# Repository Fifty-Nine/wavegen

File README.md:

Introduction
============

This is an implementation of a USB-controlled Analog Devices AD9837-based 
function generator that can generate sine, triangle and square waves up to 
around 200 kHz or so, 1 MHz if the output filtering capacitor is removed
(although the quantization of the ADC starts to become apparent around
500 kHz).

Connectors, Jumpers and Indicators
==================================

There are several off-board connectors, one jumper and three
LEDs.

| Reference    | Purpose                                    |
| ------------ | ------------------------------------------ |
| J1           | Micro-B USB Connector                      |
| J2           | External clock input                       |
| J3           | Function generator output (0.6Vpp typical) |
| J4           | FTDI channel B breakout                    |
| TP1          | USB supply voltage (5V typical, 15V max)   |
| TP2          | GND                                        |
| TP3          | LD1117 output (3.3V nominal)               |
| TP4          | Function generator output (0.6Vpp typical  |
| JP1          | Clock select jumper                        |
| D1           | LD1117 power indicator                     |
| D2           | Currently unused                           |
| D3           | Currently unused                           |

At some point I'll document the pinout for the J4 connector here.
Until then the pinout is available in the schematic.

Indicators D2 and D3 were originally intended as SPI TX/RX indicators, but
that was before I realized that the FT2232H only enables them for UART
communication (and also that the AD 9837 has no TX...). There's nothing
stopping the control software from using them for other purposes, although
the silkscreen on rev. 2 would be misleading.

Firmware
========

Because the design is based on the FTDI FT2232H, there's no firmware per se.
However, the control software looks for certain USB product and manufacturer
strings to differentiate the device from other FTDI devices. A template for
the FTDI 'FT_Prog' EEPROM programming software is provided in the `firmware/`
directory. The device should be programmed with this template before attempting
to use the control software.

Control Software
================

The control software is a work in progress, but the device can currently be
fully controlled via a provided software library. The library is written in
C++ and requires a compiler with C++11 support.

To build the library, you will need CMake and a suitable C++ compiler. On
linux, the build steps go something like this:

```
$ sudo apt-get install git build-essential cmake libftdi-dev
...
$ git clone git@github.com:Fifty-Nine/wavegen
...
$ cd wavegen/software
$ mkdir build
$ cd build
$ cmake ..
...
$ make
...
$ sudo make install
...
$
```

At this point, you can use the `wavegen-test` program to confirm that the device
is working. The test program initializes the device and repeatedly performs a
frequency sweep.

Future Work
===========

A GUI control interface would be nice to have. 

One major limitation of the current hardware is that it provides no output
amplitude control or amplification. At some point I would like to design
an amplification stage with automatic gain control. Rev 3 will allow
arbitrary waveform generation, so this will be mitigated somewhat.

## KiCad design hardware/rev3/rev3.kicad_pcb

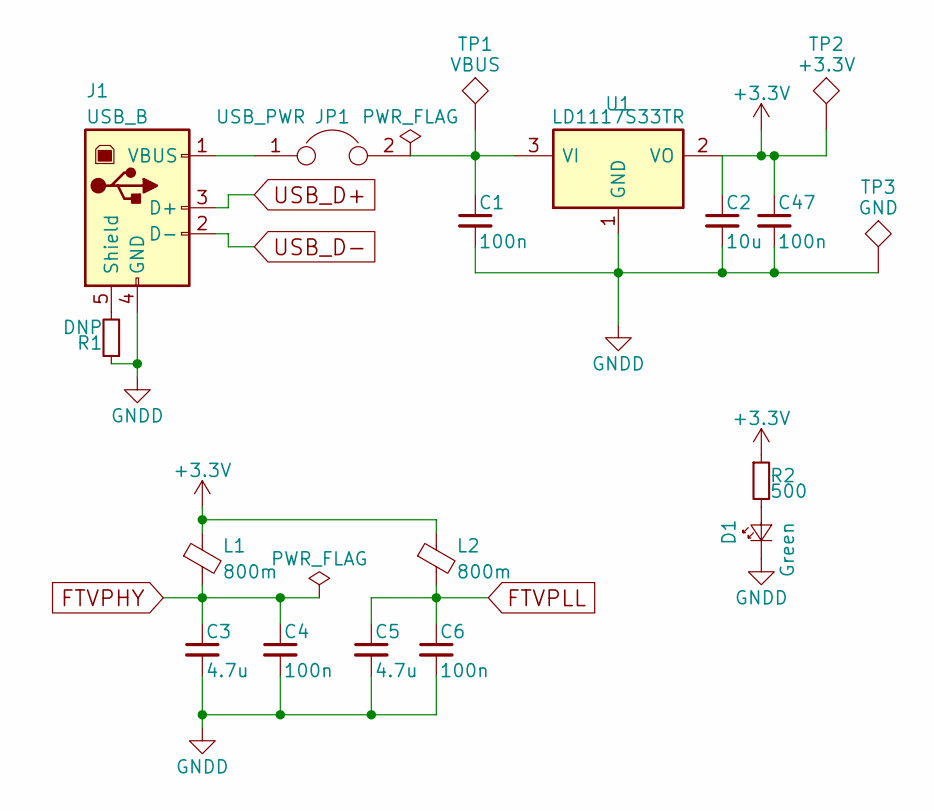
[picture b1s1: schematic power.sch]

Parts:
C1, C4, C6, C47: 100n; C_0603_HandSoldering; DigiKey 478-1395-1-ND
C2: 10u; C_0603_HandSoldering; DigiKey 478-10568-1-ND
C3, C5: 4.7u; C_0603_HandSoldering; DigiKey 478-1415-1-ND
D1: Green; LED_0805; DigiKey 350-2900-ND
J1: USB_B; USB_Micro-B-circular; DigiKey 609-4618-1-ND
JP1: USB_PWR; Pin_Header_Straight_1x02_Pitch2.54mm
L1, L2: 800m; L_0603_HandSoldering; DigiKey 490-1054-1-ND
R1: DNP; R_0603_HandSoldering; DigiKey DNP
R2: 500; R_0603_HandSoldering; DigiKey P470ADCT-ND
TP1: VBUS; Test_Point_Keystone_5005-5009_Compact; DigiKey 36-5009-ND
TP2: +3.3V; Test_Point_Keystone_5005-5009_Compact; DigiKey 36-5005-ND
TP3: GND; Test_Point_Keystone_5005-5009_Compact; DigiKey 36-5006-ND
U1: LD1117S33TR; SOT-223; DigiKey 497-1242-1-ND

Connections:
+3V3: C2.1, C47.1, L1.1, L2.1, R2.1, TP2.1, U1.2 (VO); also elsewhere on the board
FTVPHY: C3.1, C4.1, L1.2; also elsewhere on the board
FTVPLL: C5.1, C6.1, L2.2; also elsewhere on the board
GNDA: C1.2, C2.2, C3.2, C4.2, C5.2, C6.2, C47.2, D1.1 (K), J1.4 (GND), R1.1, TP3.1, U1.1 (GND); also elsewhere on the board
unnamed: C1.1, JP1.2, TP1.1, U1.3 (VI)
unnamed: D1.2 (A), R2.2
unnamed: J1.1 (VBUS), JP1.1
unnamed: J1.5 (Shield), R1.2
USB_D+: J1.3 (D+); also elsewhere on the board
USB_D-: J1.2 (D-); also elsewhere on the board

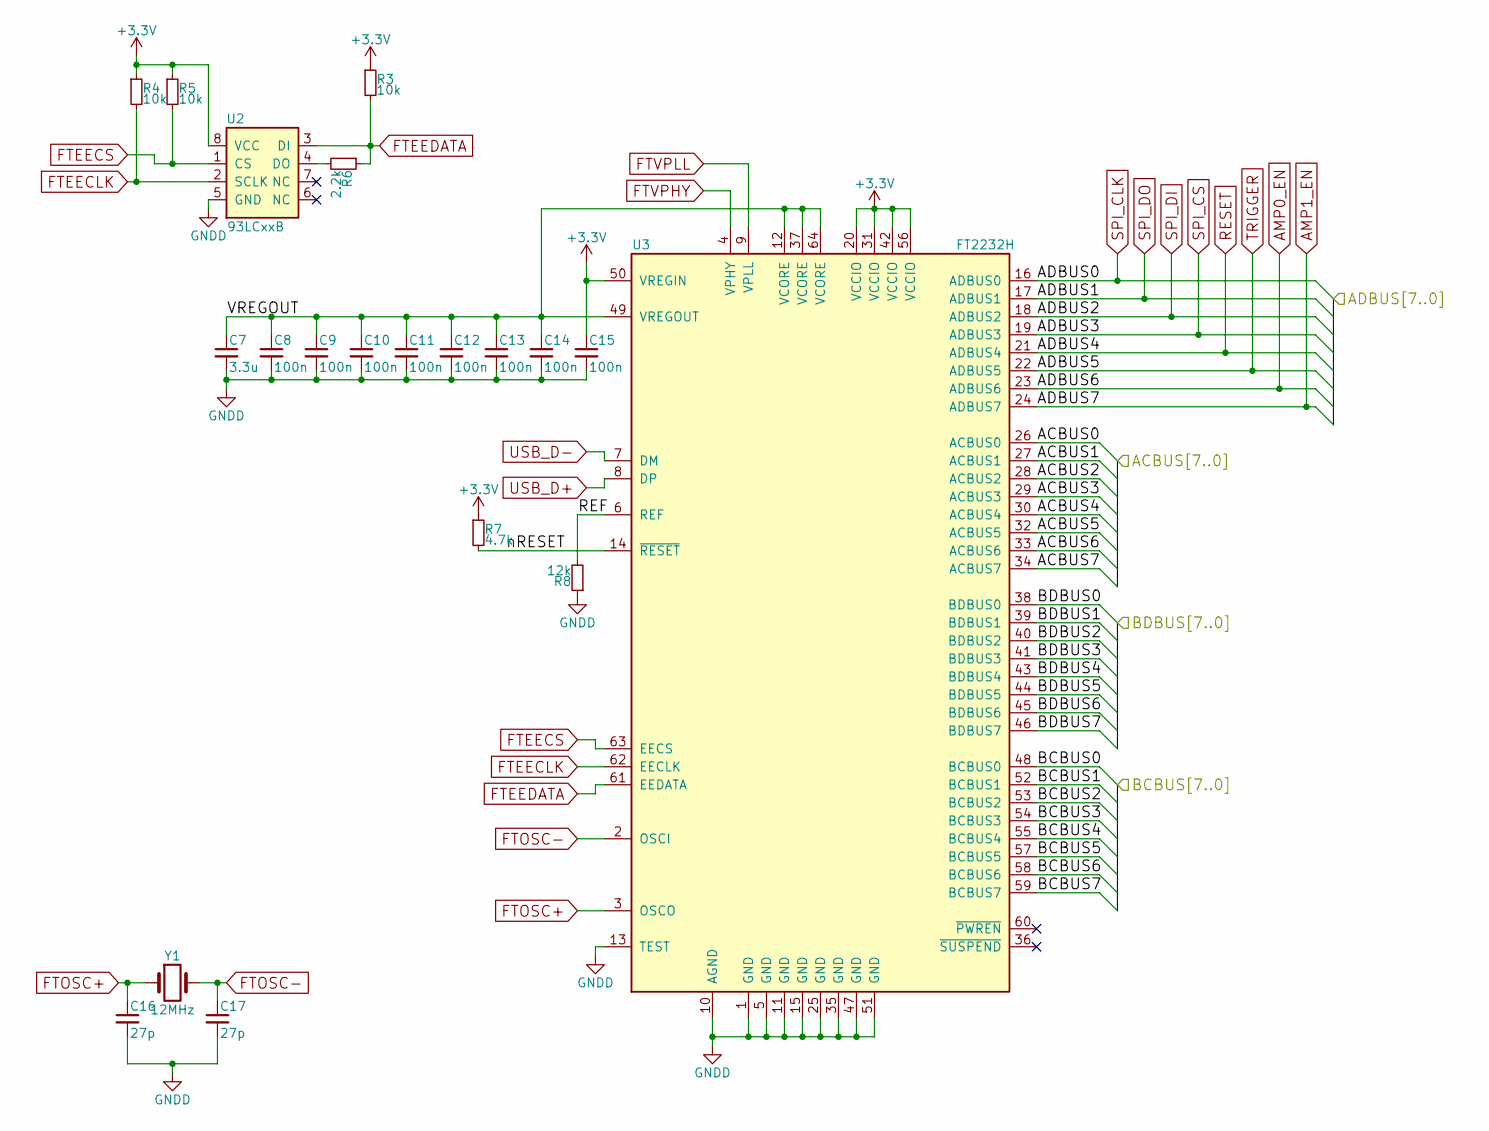
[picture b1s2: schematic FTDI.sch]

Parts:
C7: 3.3u; C_0805; DigiKey 478-1414-1-ND
C8, C9, C10, C11, C12, C13, C14, C15: 100n; C_0805; DigiKey 478-1395-1-ND
C16, C17: 27p; C_0805; DigiKey 478-10518-1-ND
R3, R4, R5: 10k; R_0805; DigiKey P10KADCT-ND
R6: 2.2k; R_0805; DigiKey P2.2KADCT-ND
R7: 4.7k; R_0805; DigiKey P1.0KADCT-ND
R8: 12k; R_0805; DigiKey P12KADCT-ND
U2: 93LCxxB; SOIC-8_3.9x4.9mm_Pitch1.27mm; DigiKey 93LC46B/SN-ND
U3: FT2232H; LQFP-64_10x10mm_Pitch0.5mm
Y1: 12MHz; Crystal_SMD_5032-2pin_5.0x3.2mm; DigiKey 535-10634-1-ND

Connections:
+3V3: C15.1, R3.1, R4.1, R5.1, R7.1, U2.8 (VCC), U3.20 (VCCIO), U3.31 (VCCIO), U3.42 (VCCIO), U3.50 (VREGIN), U3.56 (VCCIO); also elsewhere on the board
/Connectors/ACBUS0: U3.26 (ACBUS0); also elsewhere on the board
/Connectors/ACBUS1: U3.27 (ACBUS1); also elsewhere on the board
/Connectors/ACBUS2: U3.28 (ACBUS2); also elsewhere on the board
/Connectors/ACBUS3: U3.29 (ACBUS3); also elsewhere on the board
/Connectors/ACBUS4: U3.30 (ACBUS4); also elsewhere on the board
/Connectors/ACBUS5: U3.32 (ACBUS5); also elsewhere on the board
/Connectors/ACBUS6: U3.33 (ACBUS6); also elsewhere on the board
/Connectors/ACBUS7: U3.34 (ACBUS7); also elsewhere on the board
/Connectors/BCBUS0: U3.48 (BCBUS0); also elsewhere on the board
/Connectors/BCBUS1: U3.52 (BCBUS1); also elsewhere on the board
/Connectors/BCBUS2: U3.53 (BCBUS2); also elsewhere on the board
/Connectors/BCBUS3: U3.54 (BCBUS3); also elsewhere on the board
/Connectors/BCBUS4: U3.55 (BCBUS4); also elsewhere on the board
/Connectors/BCBUS5: U3.57 (BCBUS5); also elsewhere on the board
/Connectors/BCBUS6: U3.58 (BCBUS6); also elsewhere on the board
/Connectors/BCBUS7: U3.59 (BCBUS7); also elsewhere on the board
/Connectors/BDBUS0: U3.38 (BDBUS0); also elsewhere on the board
/Connectors/BDBUS1: U3.39 (BDBUS1); also elsewhere on the board
/Connectors/BDBUS2: U3.40 (BDBUS2); also elsewhere on the board
/Connectors/BDBUS3: U3.41 (BDBUS3); also elsewhere on the board
/Connectors/BDBUS4: U3.43 (BDBUS4); also elsewhere on the board
/Connectors/BDBUS5: U3.44 (BDBUS5); also elsewhere on the board
/Connectors/BDBUS6: U3.45 (BDBUS6); also elsewhere on the board
/Connectors/BDBUS7: U3.46 (BDBUS7); also elsewhere on the board
/FTDI/REF: R8.2, U3.6 (REF)
/FTDI/VREGOUT: C7.1, C8.1, C9.1, C10.1, C11.1, C12.1, C13.1, C14.1, U3.12 (VCORE), U3.37 (VCORE), U3.49 (VREGOUT), U3.64 (VCORE)
/FTDI/nRESET: R7.2, U3.14 (~RESET)
AMP0_EN: U3.23 (ADBUS6); also elsewhere on the board
AMP1_EN: U3.24 (ADBUS7); also elsewhere on the board
FTEECLK: R4.2, U2.2 (SCLK), U3.62 (EECLK)
FTEECS: R5.2, U2.1 (CS), U3.63 (EECS)
FTEEDATA: R3.2, R6.1, U2.3 (DI), U3.61 (EEDATA)
FTOSC+: C16.1, U3.3 (OSCO), Y1.1
FTOSC-: C17.1, U3.2 (OSCI), Y1.2
FTVPHY: U3.4 (VPHY); also elsewhere on the board
FTVPLL: U3.9 (VPLL); also elsewhere on the board
GNDA: C7.2, C8.2, C9.2, C10.2, C11.2, C12.2, C13.2, C14.2, C15.2, C16.2, C17.2, R8.1, U2.5 (GND), U3.1 (GND), U3.5 (GND), U3.10 (AGND), U3.11 (GND), U3.13 (TEST), U3.15 (GND), U3.25 (GND), U3.35 (GND), U3.47 (GND), U3.51 (GND); also elsewhere on the board
unnamed: R6.2, U2.4 (DO)
RESET: U3.21 (ADBUS4); also elsewhere on the board
SPI_CLK: U3.16 (ADBUS0); also elsewhere on the board
SPI_CS: U3.19 (ADBUS3); also elsewhere on the board
SPI_DI: U3.18 (ADBUS2); also elsewhere on the board
SPI_DO: U3.17 (ADBUS1); also elsewhere on the board
TRIGGER: U3.22 (ADBUS5); also elsewhere on the board
USB_D+: U3.8 (DP); also elsewhere on the board
USB_D-: U3.7 (DM); also elsewhere on the board

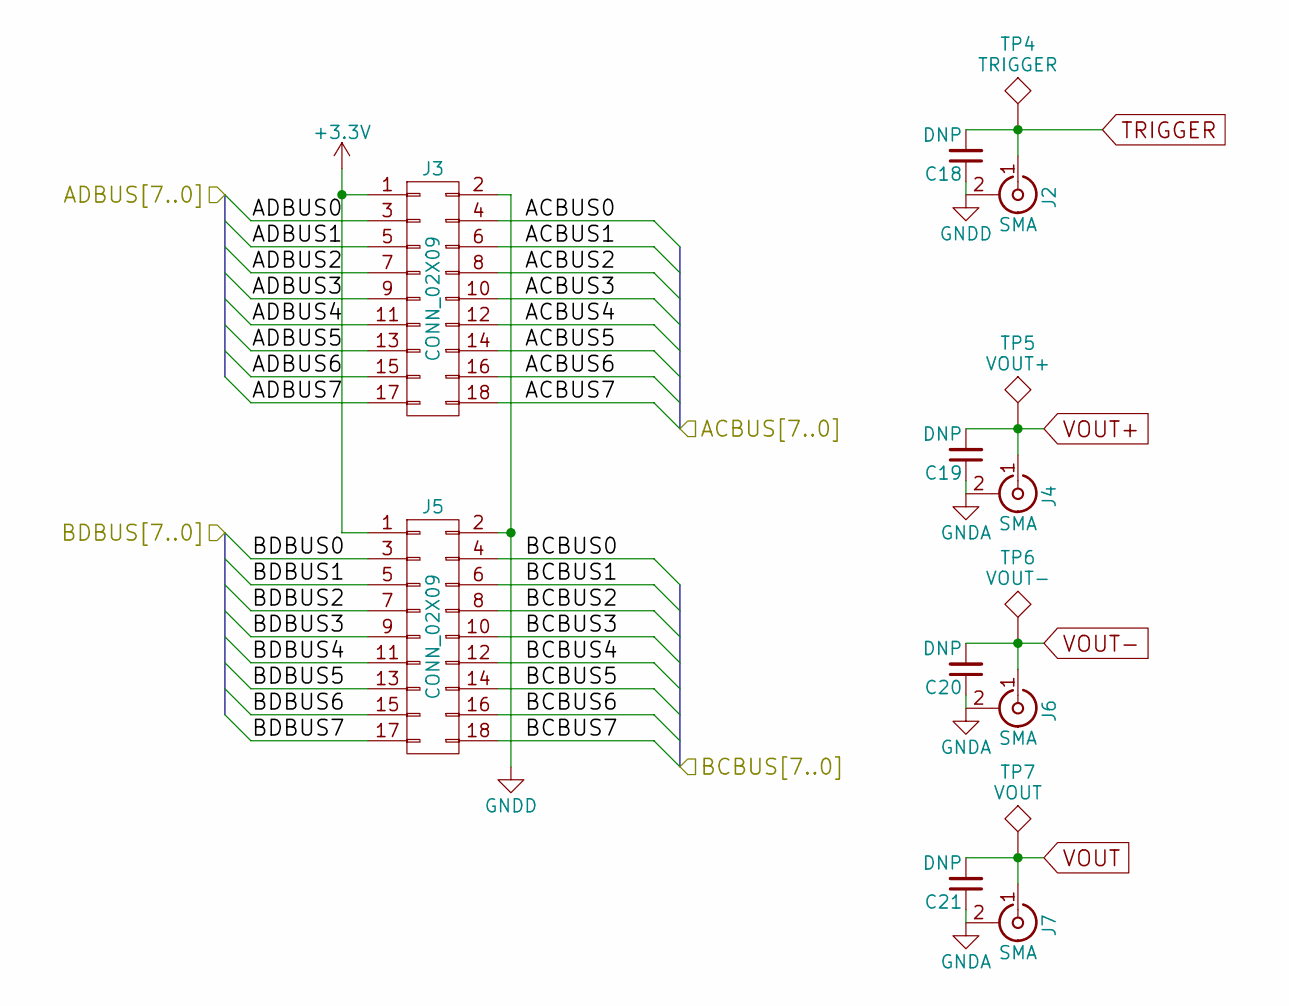
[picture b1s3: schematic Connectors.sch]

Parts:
C18, C19, C20, C21: DNP; C_0603_HandSoldering
J2: SMA; SMA_THT_Jack_Straight
J3, J5: CONN_02X09; Pin_Header_Straight_2x09_Pitch2.54mm; DigiKey S2011EC-40-ND
J4, J6, J7: SMA; Molex_SMA_Jack_Edge_Mount
TP4: TRIGGER; Test_Point_Keystone_5005-5009_Compact
TP5: VOUT+; Test_Point_Keystone_5005-5009_Compact
TP6: VOUT-; Test_Point_Keystone_5005-5009_Compact
TP7: VOUT; Test_Point_Keystone_5005-5009_Compact

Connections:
+3V3: J3.1, J5.1; also elsewhere on the board
/Connectors/ACBUS0: J3.4; also elsewhere on the board
/Connectors/ACBUS1: J3.6; also elsewhere on the board
/Connectors/ACBUS2: J3.8; also elsewhere on the board
/Connectors/ACBUS3: J3.10; also elsewhere on the board
/Connectors/ACBUS4: J3.12; also elsewhere on the board
/Connectors/ACBUS5: J3.14; also elsewhere on the board
/Connectors/ACBUS6: J3.16; also elsewhere on the board
/Connectors/ACBUS7: J3.18; also elsewhere on the board
/Connectors/BCBUS0: J5.4; also elsewhere on the board
/Connectors/BCBUS1: J5.6; also elsewhere on the board
/Connectors/BCBUS2: J5.8; also elsewhere on the board
/Connectors/BCBUS3: J5.10; also elsewhere on the board
/Connectors/BCBUS4: J5.12; also elsewhere on the board
/Connectors/BCBUS5: J5.14; also elsewhere on the board
/Connectors/BCBUS6: J5.16; also elsewhere on the board
/Connectors/BCBUS7: J5.18; also elsewhere on the board
/Connectors/BDBUS0: J5.3; also elsewhere on the board
/Connectors/BDBUS1: J5.5; also elsewhere on the board
/Connectors/BDBUS2: J5.7; also elsewhere on the board
/Connectors/BDBUS3: J5.9; also elsewhere on the board
/Connectors/BDBUS4: J5.11; also elsewhere on the board
/Connectors/BDBUS5: J5.13; also elsewhere on the board
/Connectors/BDBUS6: J5.15; also elsewhere on the board
/Connectors/BDBUS7: J5.17; also elsewhere on the board
AMP0_EN: J3.15; also elsewhere on the board
AMP1_EN: J3.17; also elsewhere on the board
GNDA: C18.1, C19.1, C20.1, C21.1, J2.2 (Ext), J3.2, J4.2 (Ext), J5.2, J6.2 (Ext), J7.2 (Ext); also elsewhere on the board
RESET: J3.11; also elsewhere on the board
SPI_CLK: J3.3; also elsewhere on the board
SPI_CS: J3.9; also elsewhere on the board
SPI_DI: J3.7; also elsewhere on the board
SPI_DO: J3.5; also elsewhere on the board
TRIGGER: C18.2, J2.1 (In), J3.13, TP4.1; also elsewhere on the board
VOUT: C21.2, J7.1 (In), TP7.1; also elsewhere on the board
VOUT+: C19.2, J4.1 (In), TP5.1; also elsewhere on the board
VOUT-: C20.2, J6.1 (In), TP6.1; also elsewhere on the board

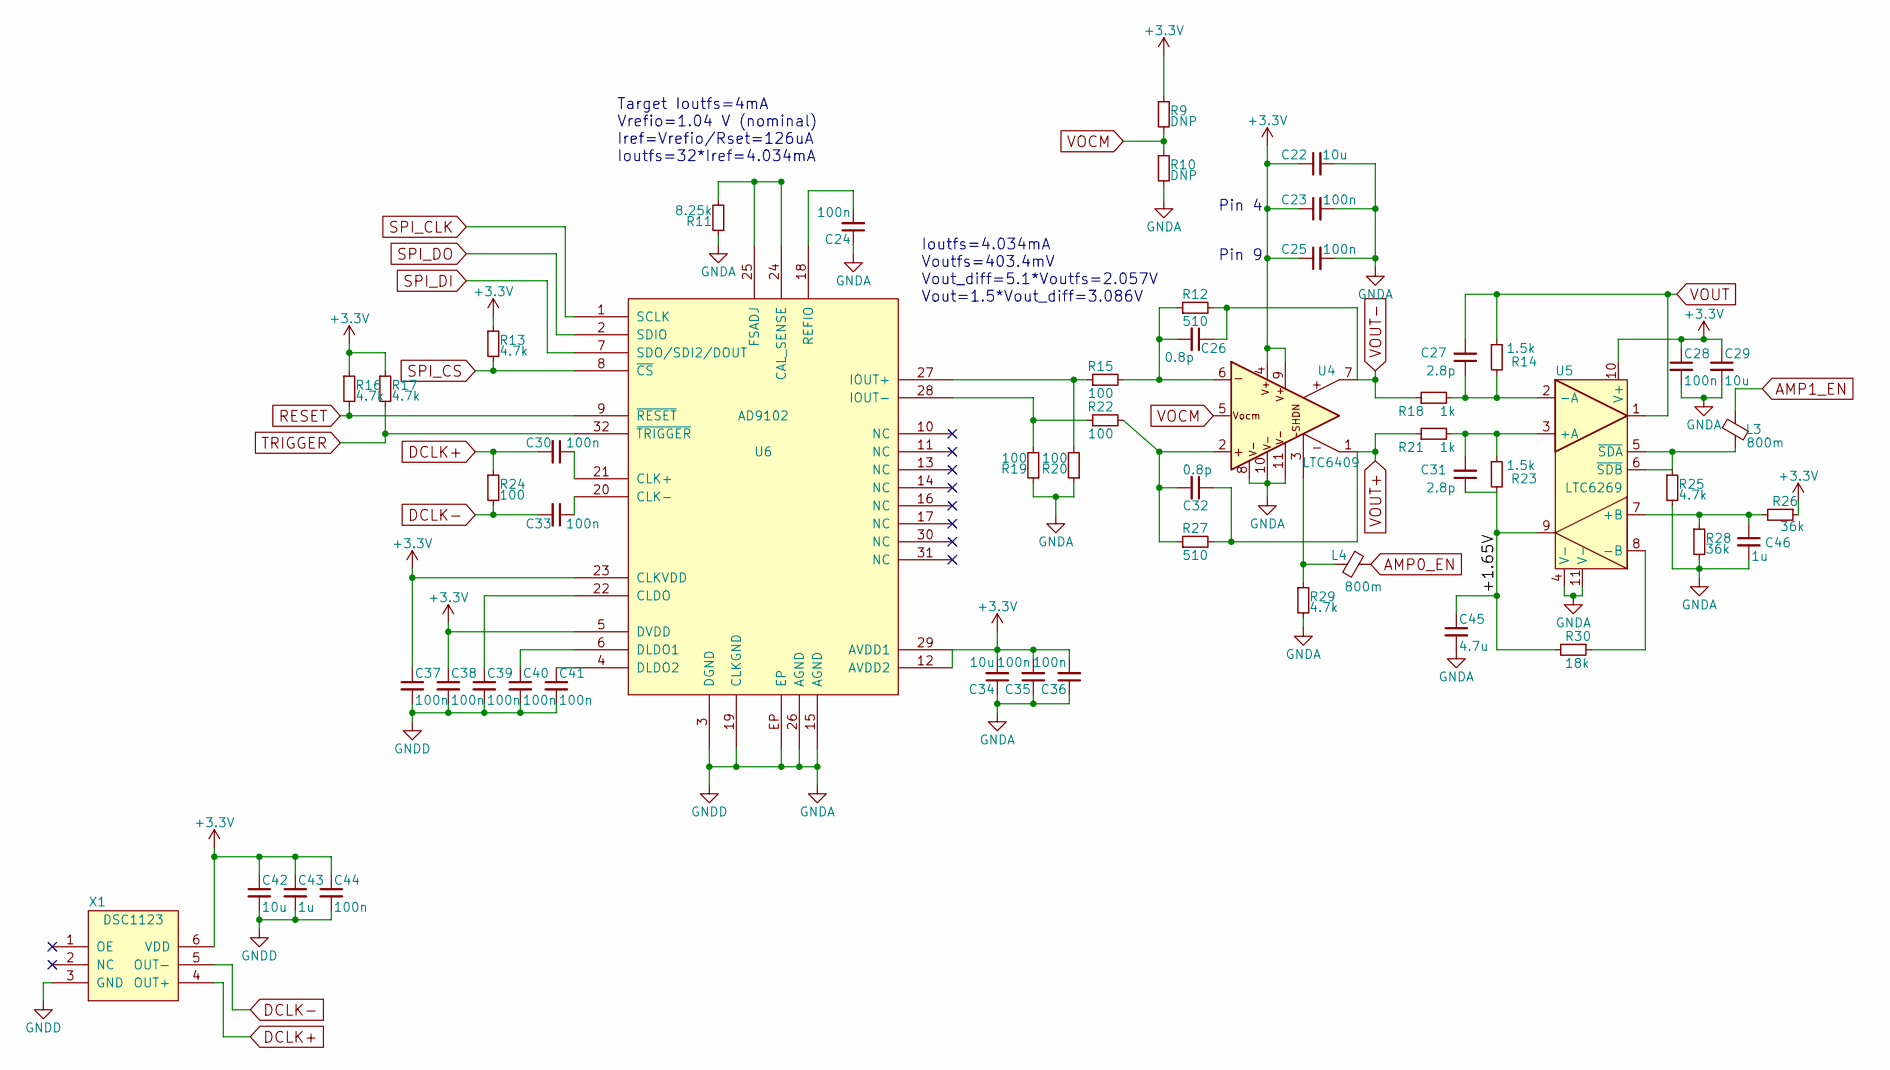
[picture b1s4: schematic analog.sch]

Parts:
C22, C29, C34, C42: 10u; C_0603_HandSoldering
C23, C24, C25, C28, C30, C33, C35, C36, C37, C38, C39, C40, C41, C44: 100n; C_0603_HandSoldering
C26, C32: 0.8p; C_0603_HandSoldering
C27, C31: 2.8p; C_0603_HandSoldering
C43, C46: 1u; C_0603_HandSoldering
C45: 4.7u; C_0603_HandSoldering
L3, L4: 800m; L_0603_HandSoldering
R9, R10: DNP; R_0603_HandSoldering
R11: 8.25k; R_0603_HandSoldering
R12, R27: 510; R_0603_HandSoldering
R13, R16, R17, R25, R29: 4.7k; R_0603_HandSoldering
R14, R23: 1.5k; R_0603_HandSoldering
R15, R19, R20, R22, R24: 100; R_0603_HandSoldering
R18, R21: 1k; R_0603_HandSoldering
R26, R28: 36k; R_0603_HandSoldering
R30: 18k; R_0603_HandSoldering
U4: LTC6409; LTC6409-UDB
U5: LTC6269; LTC6269-10DFN
U6: AD9102; AD9102-10LFCSP; DigiKey AD9102BCPZ-ND
X1: DSC1123; 7050XO; DigiKey 576-4642-ND

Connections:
+3V3: C22.1, C23.1, C25.1, C28.1, C29.1, C34.2, C35.2, C36.2, C37.1, C38.1, C42.1, C43.1, C44.1, R9.1, R13.1, R16.1, R17.1, R26.1, U4.4, U4.9, U5.10 (V+), U6.5 (DVDD), U6.12 (AVDD2), U6.23 (CLKVDD), U6.29 (AVDD1), X1.6 (VDD); also elsewhere on the board
/Analog/+1.65V: C31.1, C45.1, R23.2, R30.2, U5.9
AMP0_EN: L4.1; also elsewhere on the board
AMP1_EN: L3.2; also elsewhere on the board
DCLK+: C30.2, R24.1, X1.4 (OUT+)
DCLK-: C33.2, R24.2, X1.5 (OUT-)
GNDA: C22.2, C23.2, C24.1, C25.2, C28.2, C29.2, C34.1, C35.1, C36.1, C37.2, C38.2, C39.2, C40.2, C41.2, C42.2, C43.2, C44.2, C45.2, C46.2, R10.2, R11.1, R19.1, R20.1, R25.2, R28.2, R29.2, U4.8, U4.10, U4.11, U5.4 (V-), U5.11 (V-), U6.3 (DGND), U6.15 (AGND), U6.19 (CLKGND), U6.26 (AGND), U6.EP, X1.3 (GND); also elsewhere on the board
unnamed: C24.2, U6.18 (REFIO)
unnamed: C26.2, R12.1, R15.2, U4.6
unnamed: C27.1, R14.2, R18.2, U5.2 (-A)
unnamed: C30.1, U6.21 (CLK+)
unnamed: C31.2, R21.2, R23.1, U5.3 (+A)
unnamed: C32.2, R22.2, R27.1, U4.2
unnamed: C33.1, U6.20 (CLK-)
unnamed: C39.1, U6.22 (CLDO)
unnamed: C40.1, U6.6 (DLDO1)
unnamed: C41.1, U6.4 (DLDO2)
unnamed: C46.1, R26.2, R28.1, U5.7 (+B)
unnamed: L3.1, R25.1, U5.5 (~SDA), U5.6 (~SDB)
unnamed: L4.2, R29.1, U4.3
unnamed: R11.2, U6.24 (CAL_SENSE), U6.25 (FSADJ)
unnamed: R15.1, R20.2, U6.27 (IOUT+)
unnamed: R19.2, R22.1, U6.28 (IOUT-)
unnamed: R30.1, U5.8 (-B)
RESET: R16.2, U6.9 (~RESET); also elsewhere on the board
SPI_CLK: U6.1 (SCLK); also elsewhere on the board
SPI_CS: R13.2, U6.8 (~CS); also elsewhere on the board
SPI_DI: U6.7 (SDO/SDI2/DOUT); also elsewhere on the board
SPI_DO: U6.2 (SDIO); also elsewhere on the board
TRIGGER: R17.2, U6.32 (~TRIGGER); also elsewhere on the board
VOCM: R9.2, R10.1, U4.5
VOUT: C27.2, R14.1, U5.1; also elsewhere on the board
VOUT+: C32.1, R21.1, R27.2, U4.1; also elsewhere on the board
VOUT-: C26.1, R12.2, R18.1, U4.7; also elsewhere on the board

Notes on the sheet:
Pin 4
Pin 9
Target Ioutfs=4mA Vrefio=1.04 V (nominal) Iref=Vrefio/Rset=126uA Ioutfs=32*Iref=4.034mA
Ioutfs=4.034mA Voutfs=403.4mV Vout_diff=5.1*Voutfs=2.057V Vout=1.5*Vout_diff=3.086V

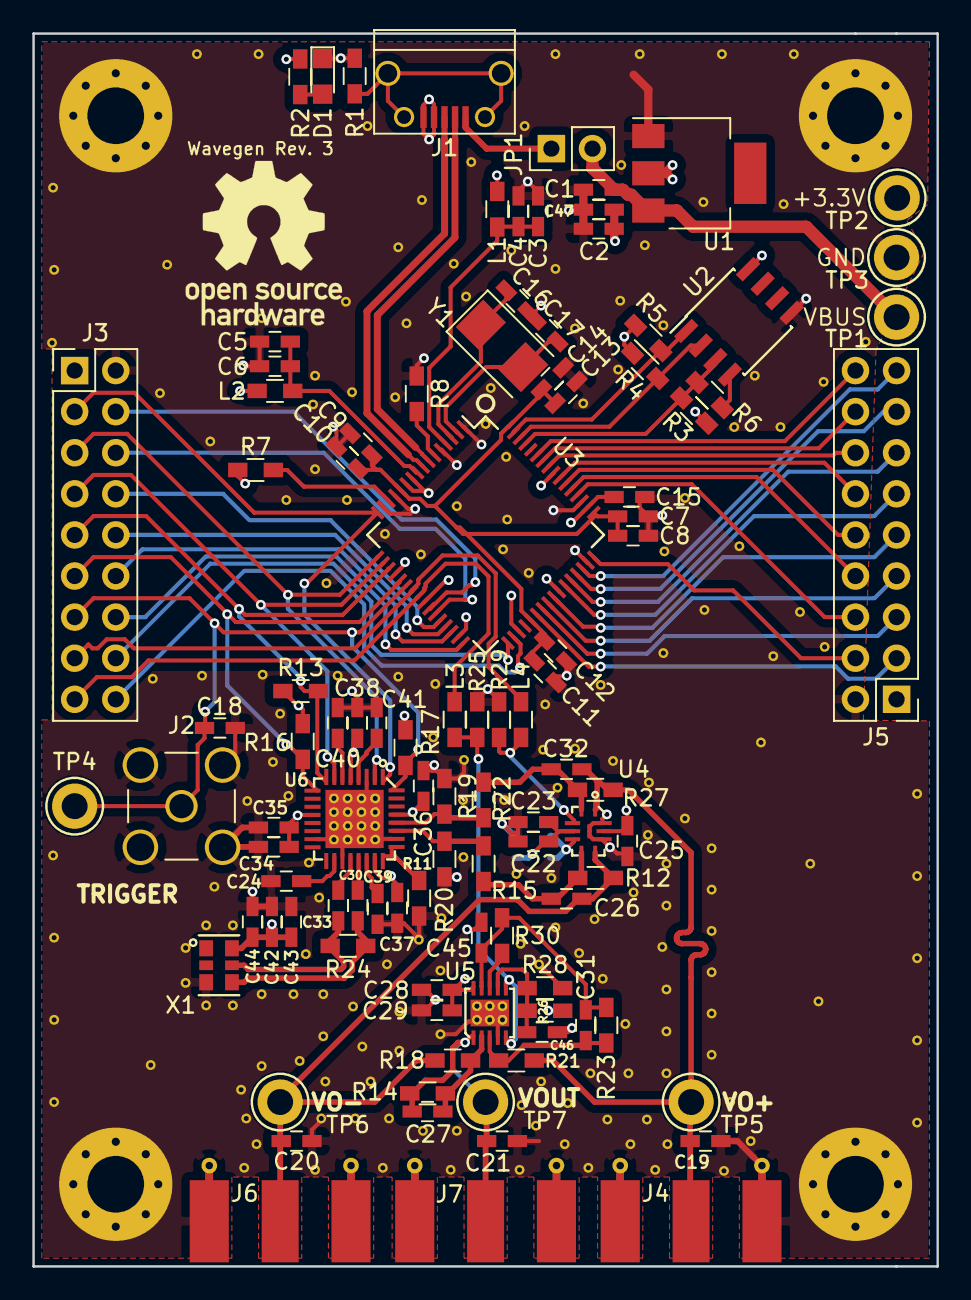
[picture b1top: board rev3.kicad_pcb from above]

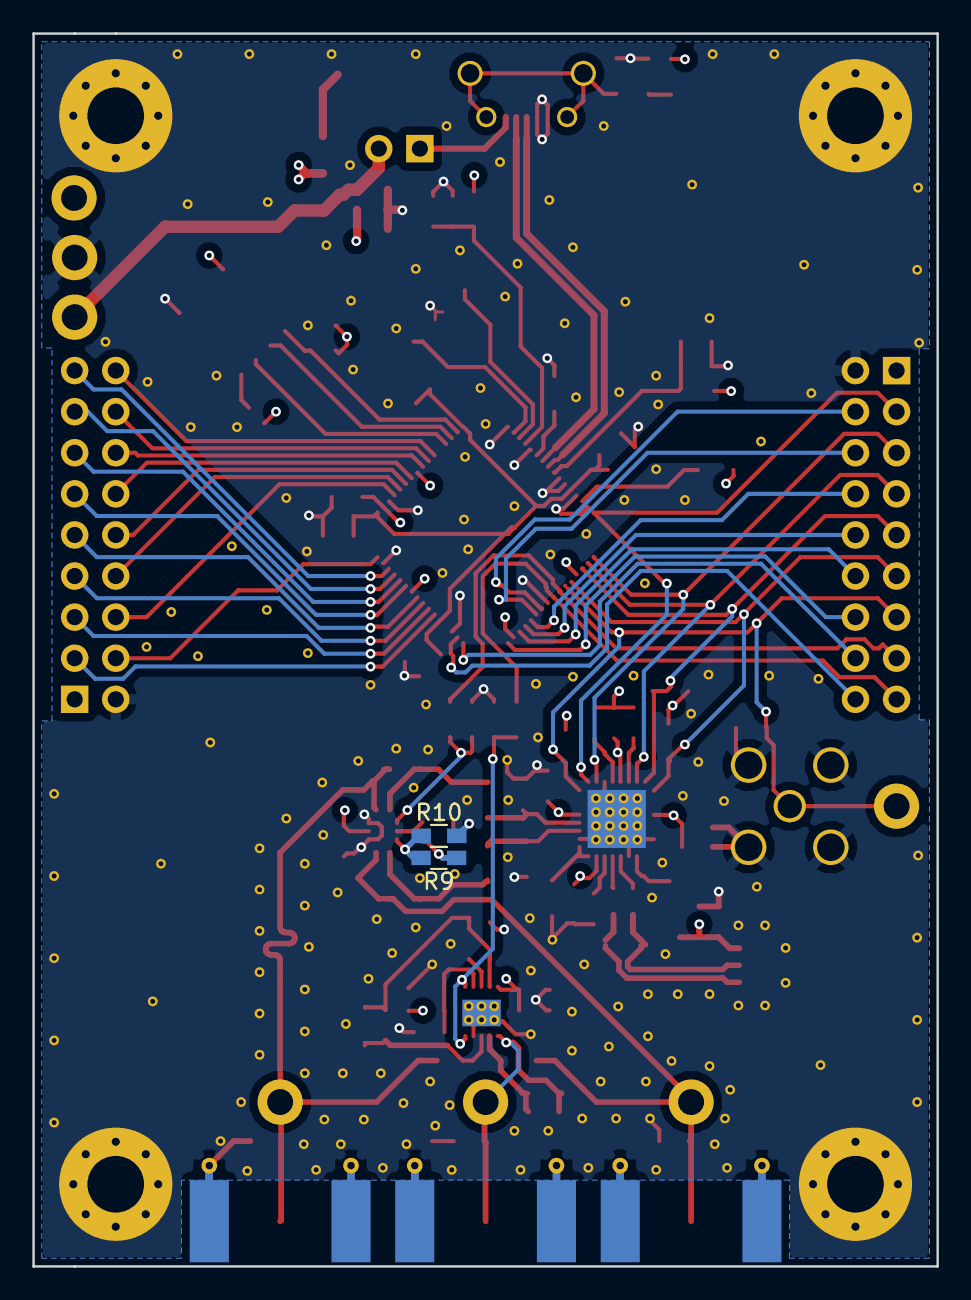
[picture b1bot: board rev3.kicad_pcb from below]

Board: 4 copper layers, 55.9 x 76.2 mm, 105 parts (2 on the bottom side), 75 nets.

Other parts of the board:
 C19: DNP; C_0603_HandSoldering

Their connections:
GNDA: C19.1; also elsewhere on the board
VOUT+: C19.2; also elsewhere on the board

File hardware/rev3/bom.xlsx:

Id | Designator | Designation | Package | Quantity | Supplier and ref
1 | D1 | Green | LED_0805 | 1 | 350-2900-ND
2 | J3;J5 | CONN_02X09 | Pin_Header_Straight_2x09_Pitch2.54mm | 2 | S2011EC-40-ND
3 | TP1 | VBUS | Test_Point_Keystone_5005-5009_Compact | 1 | 36-5009-ND
4 | TP2 | +3.3V | Test_Point_Keystone_5005-5009_Compact | 1 | 36-5005-ND
5 | TP3 | GND | Test_Point_Keystone_5005-5009_Compact | 1 | 36-5006-ND
6 | U1 | LD1117S33TR | SOT-223 | 1 | 497-1242-1-ND
7 | U2 | 93LCxxB | SOIC-8_3.9x4.9mm_Pitch1.27mm | 1 | 93LC46BT-I/SNCT-ND
8 | U3 | FT2232H | LQFP-64_10x10mm_Pitch0.5mm | 1 | 768-1024-1-ND
9 | Y1 | 12MHz | Crystal_SMD_5032-2pin_5.0x3.2mm | 1 | 535-10634-1-ND
10 | C1;C4;C6;C8-C15;C23-C25;C28;C30;C33;C35-C41;C44;C47 | 100n | C_0603_HandSoldering | 26 | 478-1239-1-ND
11 | C2;C22;C29;C34;C42 | 10u | C_0603_HandSoldering | 5 | 478-8050-1-ND
12 | C3;C5;C45 | 4.7u | C_0603_HandSoldering | 3 | 478-7943-1-ND
13 | C7 | 3.3u | C_0603_HandSoldering | 1 | 490-6411-1-ND
14 | C16;C17 | 27p | C_0603_HandSoldering | 2 | 478-1168-1-ND
15 | C26;C32 | 0.8p | C_0603_HandSoldering | 2 | 478-6730-1-ND
16 | C27;C31 | 2.8p | C_0603_HandSoldering | 2 | 478-3840-1-ND
17 | C43;C46 | 1u | C_0603_HandSoldering | 2 | 478-5010-2-ND
18 | J2 | SMA | SMA_THT_Jack_Straight | 1 | A97594-ND
19 | J4;J6;J7 | SMA | Molex_SMA_Jack_Edge_Mount | 3 | WM5534-ND
20 | L1;L2;L3;L4 | 800m | L_0603_HandSoldering | 4 | 490-5255-1-ND
21 | R3;R4;R5 | 10k | R_0603_HandSoldering | 3 | P10KBZCT-ND
22 | R6 | 2.2k | R_0603_HandSoldering | 1 | P2.2KBZCT-ND
23 | R7;R13;R16;R17;R25;R29 | 4.7k | R_0603_HandSoldering | 6 | P4.7KBZCT-ND
24 | R8 | 12k | R_0603_HandSoldering | 1 | P12.0KHCT-ND
25 | R11 | 8.25k | R_0603_HandSoldering | 1 | P8.25KDBCT-ND
26 | R2;R12;R27 | 510 | R_0603_HandSoldering | 3 | P510BYCT-ND
27 | R14;R23 | 1.5k | R_0603_HandSoldering | 2 | P1.5KBYCT-ND
28 | R15;R19;R20;R22;R24 | 100 | R_0603_HandSoldering | 5 | P100BYCT-ND
29 | R18;R21 | 1k | R_0603_HandSoldering | 2 | P1.0KBYCT-ND
30 | R26;R28 | 36k | R_0603_HandSoldering | 2 | P20459CT-ND
31 | TP4 | TRIGGER | Test_Point_Keystone_5005-5009_Compact | 1 | 36-5122-ND
32 | TP5 | VOUT+ | Test_Point_Keystone_5005-5009_Compact | 1 | 36-5005-ND
33 | TP6 | VOUT- | Test_Point_Keystone_5005-5009_Compact | 1 | 36-5007-ND
34 | TP7 | VOUT | Test_Point_Keystone_5005-5009_Compact | 1 | 36-5121-ND
35 | U4 | LTC6409 | LTC6409-UDB | 1 | LTC6409CUDB#TRMPBFCT-ND
36 | U5 | LTC6269 | LTC6269-10DFN | 1 | LTC6269HDD#PBF-ND
37 | U6 | AD9102 | AD9102-10LFCSP | 1 | AD9102BCPZ-ND
38 | X1 | DSC1123 | 3225XO | 1 | 576-4649-ND
39 | R30 | 18k | R_0603_HandSoldering | 1 | P20424CT-ND
40 | J1 | USB_B | USB_Micro-B-circular | 1 | 609-4618-1-ND
41 | JP1 | USB_PWR | Pin_Header_Straight_1x02_Pitch2.54mm | 1
42 | C18;C19;C20;C21 | DNP | C_0603_HandSoldering | 4
43 | R1;R9;R10 | DNP | R_0603_HandSoldering | 3
 |  |  |  | 97

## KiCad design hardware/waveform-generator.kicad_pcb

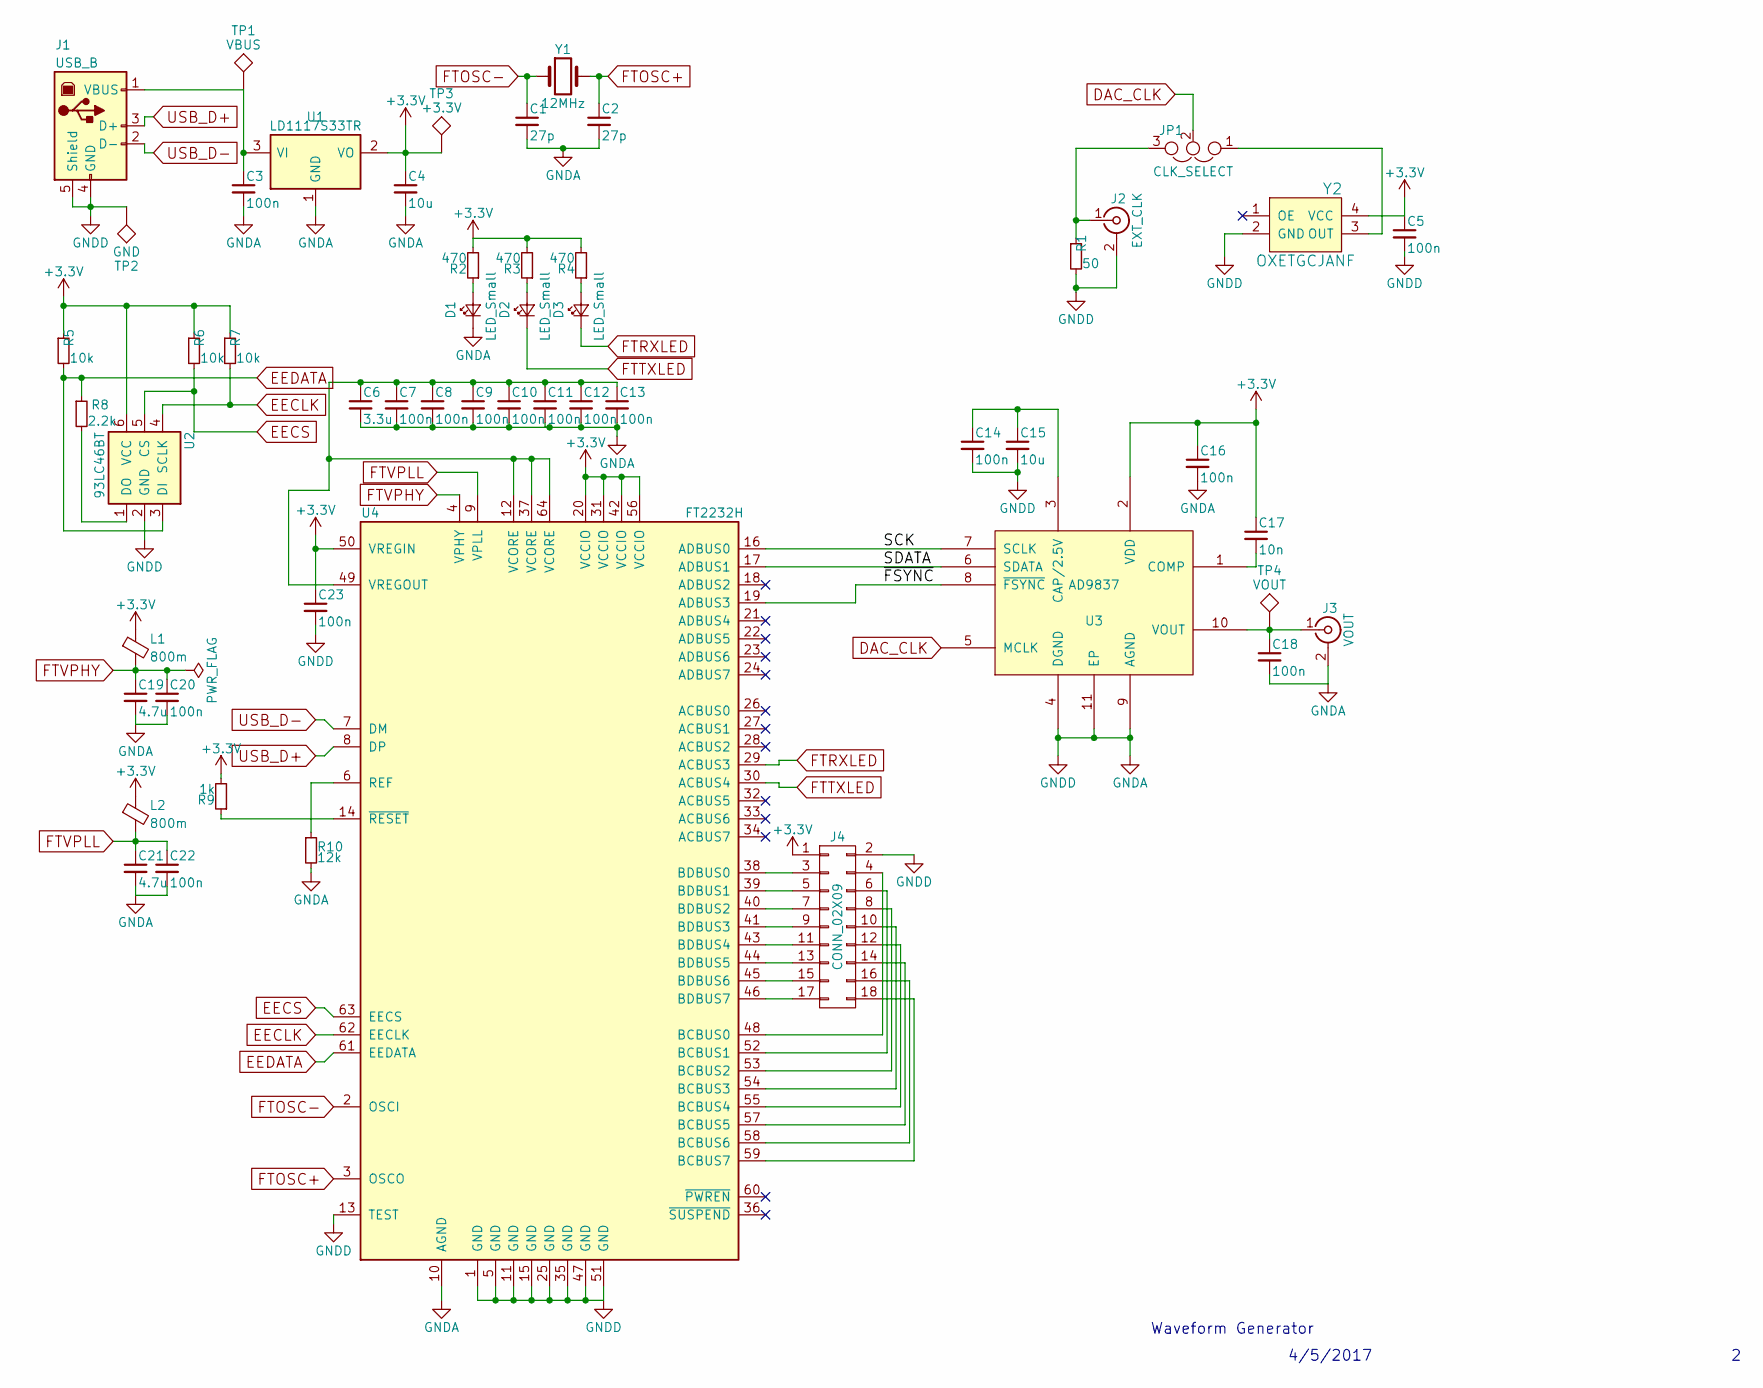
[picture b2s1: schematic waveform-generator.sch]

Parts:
C1, C2: 27p; C_0805_HandSoldering
C3, C5, C7, C8, C9, C10, C11, C12, C13, C14, C16, C18, C20, C22, C23: 100n; C_0805_HandSoldering
C4, C15: 10u; C_0805_HandSoldering
C6: 3.3u; C_0805_HandSoldering
C17: 10n; C_0805_HandSoldering
C19, C21: 4.7u; C_0805_HandSoldering
D1, D2, D3: LED_Small; LED_0805
J1: USB_B; USB_Micro-B
J2: EXT_CLK; SMA_THT_Jack_Straight
J3: VOUT; SMA_THT_Jack_Straight
J4: CONN_02X09; Pin_Header_Straight_2x09_Pitch2.54mm
JP1: CLK_SELECT; Pin_Header_Straight_1x03_Pitch2.54mm
L1, L2: 800m; L_0805_HandSoldering
R1: 50; R_0603_HandSoldering
R2, R3, R4: 470; R_0805_HandSoldering
R5, R6, R7: 10k; R_0805_HandSoldering
R8: 2.2k; R_0805_HandSoldering
R9: 1k; R_0805_HandSoldering
R10: 12k; R_0805_HandSoldering
TP1: VBUS; Test_Point_Keystone_5005-5009_Compact
TP2: GND; Test_Point_Keystone_5005-5009_Compact
TP3: +3.3V; Test_Point_Keystone_5005-5009_Compact
TP4: VOUT; Test_Point_Keystone_5005-5009_Compact
U1: LD1117S33TR; SOT-223
U2: 93LC46BT; SOT-23-6_Handsoldering
U3: AD9837
U4: FT2232H; LQFP-64_10x10mm_Pitch0.5mm
Y1: 12MHz; Crystal_SMD_5032-2pin_5.0x3.2mm_HandSoldering
Y2: OXETGCJANF; Oscillator_SMD_Abracon_ASE-4pin_3.2x2.5mm_HandSoldering

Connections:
+3V3: C4.1, C5.1, C16.1, C17.1, C23.1, J4.1, L1.1, L2.1, R2.2, R3.2, R4.2, R5.1, R6.1, R7.1, R9.2, TP3.1, U1.2 (VO), U2.6 (VCC), U3.2 (VDD), U4.20 (VCCIO), U4.31 (VCCIO), U4.42 (VCCIO), U4.50 (VREGIN), U4.56 (VCCIO), Y2.4 (VCC)
/SCK: U3.7 (SCLK), U4.16 (ADBUS0)
/SDATA: U3.6 (SDATA), U4.17 (ADBUS1)
/~FSYNC: U3.8 (~FSYNC), U4.19 (ADBUS3)
DAC_CLK: JP1.2, U3.5 (MCLK)
EECLK: R7.2, U2.4 (SCLK), U4.62 (EECLK)
EECS: R6.2, U2.5 (CS), U4.63 (EECS)
EEDATA: R5.2, R8.1, U2.3 (DI), U4.61 (EEDATA)
FTOSC+: C2.1, U4.3 (OSCO), Y1.2
FTOSC-: C1.1, U4.2 (OSCI), Y1.1
FTRXLED: D3.1 (K), U4.29 (ACBUS3)
FTTXLED: D2.1 (K), U4.30 (ACBUS4)
FTVPHY: C19.1, C20.1, L1.2, U4.4 (VPHY)
FTVPLL: C21.1, C22.1, L2.2, U4.9 (VPLL)
GNDA: C1.2, C2.2, C3.2, C4.2, C5.2, C6.2, C7.2, C8.2, C9.2, C10.2, C11.2, C12.2, C13.2, C14.2, C15.2, C16.2, C18.2, C19.2, C20.2, C21.2, C22.2, C23.2, D1.1 (K), J1.4 (GND), J1.5 (Shield), J2.2 (Ext), J3.2 (Ext), J4.2, R1.2, R10.2, TP2.1, U1.1 (GND), U2.2 (GND), U3.4 (DGND), U3.9 (AGND), U3.11 (EP), U4.1 (GND), U4.5 (GND), U4.10 (AGND), U4.11 (GND), U4.13 (TEST), U4.15 (GND), U4.25 (GND), U4.35 (GND), U4.47 (GND), U4.51 (GND), Y2.2 (GND)
unnamed: C3.1, J1.1 (VBUS), TP1.1, U1.3 (VI)
unnamed: C6.1, C7.1, C8.1, C9.1, C10.1, C11.1, C12.1, C13.1, U4.12 (VCORE), U4.37 (VCORE), U4.49 (VREGOUT), U4.64 (VCORE)
unnamed: C14.1, C15.1, U3.3 (CAP/2.5V)
unnamed: C17.2, U3.1 (COMP)
unnamed: C18.1, J3.1 (In), TP4.1, U3.10 (VOUT)
unnamed: D1.2 (A), R2.1
unnamed: D2.2 (A), R3.1
unnamed: D3.2 (A), R4.1
unnamed: J2.1 (In), JP1.3, R1.1
unnamed: J4.3, U4.38 (BDBUS0)
unnamed: J4.4, U4.48 (BCBUS0)
unnamed: J4.5, U4.39 (BDBUS1)
unnamed: J4.6, U4.52 (BCBUS1)
unnamed: J4.7, U4.40 (BDBUS2)
unnamed: J4.8, U4.53 (BCBUS2)
unnamed: J4.9, U4.41 (BDBUS3)
unnamed: J4.10, U4.54 (BCBUS3)
unnamed: J4.11, U4.43 (BDBUS4)
unnamed: J4.12, U4.55 (BCBUS4)
unnamed: J4.13, U4.44 (BDBUS5)
unnamed: J4.14, U4.57 (BCBUS5)
unnamed: J4.15, U4.45 (BDBUS6)
unnamed: J4.16, U4.58 (BCBUS6)
unnamed: J4.17, U4.46 (BDBUS7)
unnamed: J4.18, U4.59 (BCBUS7)
unnamed: JP1.1, Y2.3 (OUT)
unnamed: R8.2, U2.1 (DO)
unnamed: R9.1, U4.14 (~RESET)
unnamed: R10.1, U4.6 (REF)
USB_D+: J1.3 (D+), U4.8 (DP)
USB_D-: J1.2 (D-), U4.7 (DM)

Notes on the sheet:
Waveform Generator
4/5/2017
